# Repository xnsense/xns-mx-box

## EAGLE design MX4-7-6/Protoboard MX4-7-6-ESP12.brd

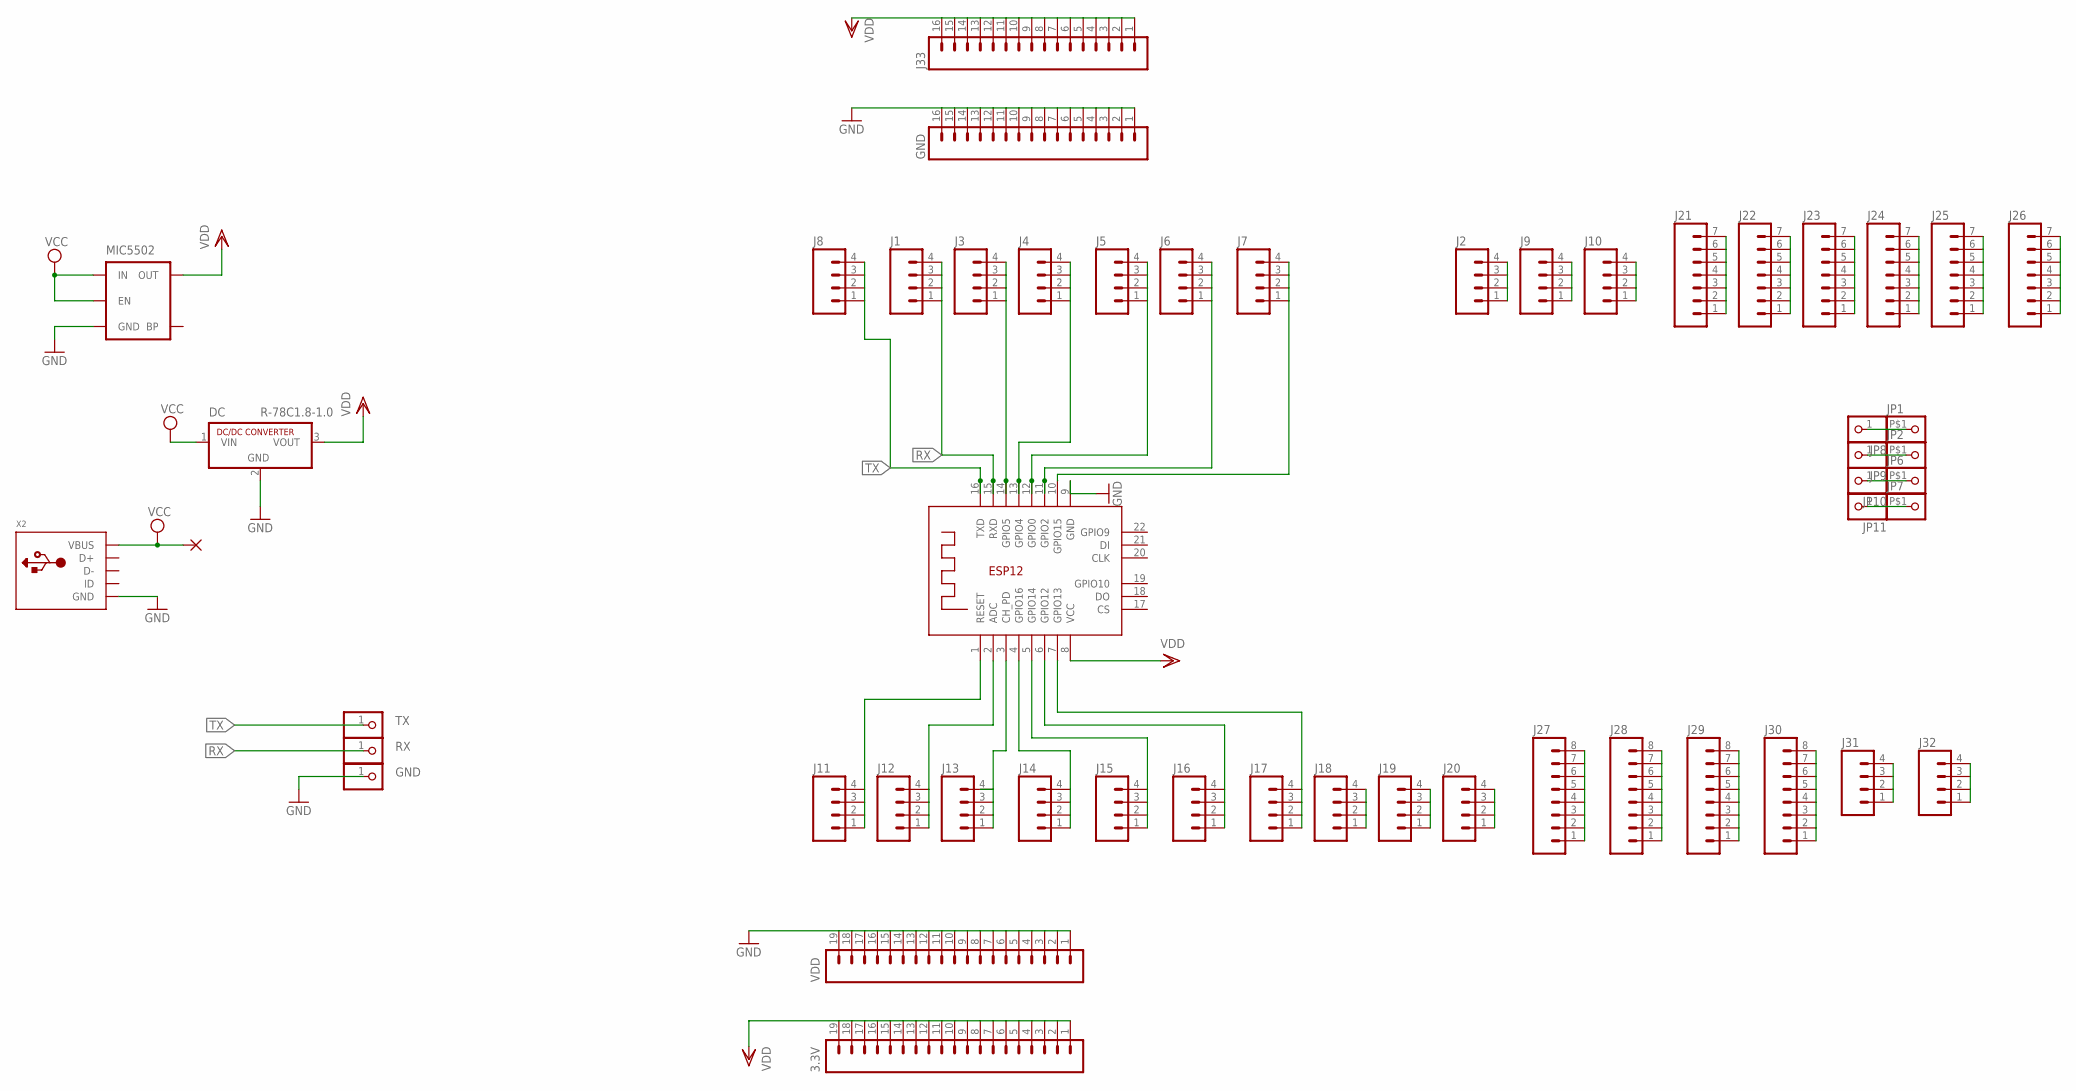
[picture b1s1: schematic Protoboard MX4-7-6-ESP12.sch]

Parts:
3.3V: M191X19_NO_SILK; 1X19_NO_SILK
5V: 1,6/0,8
DC: R-78C1.8-1.0; SIP3
GND: M161X16_NO_SILK; 1X16_NO_SILK
J1, J2, J3, J4, J5, J6, J7, J8, J9, J10, J11, J12, J13, J14, J15, J16, J17, J18, J19, J20, J31, J32: M04NO_SILK_ALL_ROUND; 1X04_NO_SILK_ALL_ROUND
J21, J22, J23, J24, J25, J26: M07NO_SILK; 1X07_NO_SILK
J27, J28, J29, J30: M08NO_SILK_FEMALE_PTH; 1X08_NO_SILK
J33: M161X16_NO_SILK; 1X16_NO_SILK
JP1, JP2, JP6, JP7: PINHD-1X1-BIGPOGO; 1X1-BIGPOGO
JP3: TX; 1X01-CLEANBIG
JP4: RX; 1X01-CLEANBIG
JP5: GND; 1X01-CLEANBIG
JP8, JP9, JP10, JP11: PINHD-1X1CB; 1X01-CLEANBIG
MIC5502: MIC52053.3V; SOT23-5
VDD: M191X19_NO_SILK; 1X19_NO_SILK
X1: ESP-12E
X2: USBMICRO_20329; 4UCONN_20329

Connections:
GND: DC.2 (GND), GND.1, GND.2, GND.3, GND.4, GND.5, GND.6, GND.7, GND.8, GND.9, GND.10, GND.11, GND.12, GND.13, GND.14, GND.15, GND.16, JP5.1, MIC5502.2 (GND), VDD.1, VDD.2, VDD.3, VDD.4, VDD.5, VDD.6, VDD.7, VDD.8, VDD.9, VDD.10, VDD.11, VDD.12, VDD.13, VDD.14, VDD.15, VDD.16, VDD.17, VDD.18, VDD.19, X1.9 (GND), X2.BASE@1 (GND), X2.BASE@2 (GND), X2.GND, X2.SPRT@1 (GND), X2.SPRT@2 (GND), X2.SPRT@3 (GND), X2.SPRT@4 (GND)
unnamed: J21.1, J21.2, J21.3, J21.4, J21.5, J21.6, J21.7
unnamed: J2.1, J2.2, J2.3, J2.4
unnamed: J3.1, J3.2, J3.3, J3.4, X1.14 (GPIO5)
unnamed: J4.1, J4.2, J4.3, J4.4, X1.13 (GPIO4)
unnamed: J5.1, J5.2, J5.3, J5.4, X1.12 (GPIO0)
unnamed: J6.1, J6.2, J6.3, J6.4, X1.11 (GPIO2)
unnamed: J7.1, J7.2, J7.3, J7.4, X1.10 (GPIO15)
unnamed: J9.1, J9.2, J9.3, J9.4
unnamed: J10.1, J10.2, J10.3, J10.4
unnamed: J18.1, J18.2, J18.3, J18.4
unnamed: J22.1, J22.2, J22.3, J22.4, J22.5, J22.6, J22.7
unnamed: J23.1, J23.2, J23.3, J23.4, J23.5, J23.6, J23.7
unnamed: J24.1, J24.2, J24.3, J24.4, J24.5, J24.6, J24.7
unnamed: J25.1, J25.2, J25.3, J25.4, J25.5, J25.6, J25.7
unnamed: J26.1, J26.2, J26.3, J26.4, J26.5, J26.6, J26.7
unnamed: J27.1, J27.2, J27.3, J27.4, J27.5, J27.6, J27.7, J27.8
unnamed: J19.1, J19.2, J19.3, J19.4
unnamed: J20.1, J20.2, J20.3, J20.4
unnamed: J28.1, J28.2, J28.3, J28.4, J28.5, J28.6, J28.7, J28.8
unnamed: J14.1, J14.2, J14.3, J14.4, X1.4 (GPIO16)
unnamed: J29.1, J29.2, J29.3, J29.4, J29.5, J29.6, J29.7, J29.8
unnamed: J30.1, J30.2, J30.3, J30.4, J30.5, J30.6, J30.7, J30.8
unnamed: J31.1, J31.2, J31.3, J31.4
unnamed: J32.1, J32.2, J32.3, J32.4
unnamed: JP1.P$1, JP8.1
unnamed: JP2.P$1, JP9.1
unnamed: JP6.P$1, JP10.1
unnamed: J17.1, J17.2, J17.3, J17.4, X1.7 (GPIO13)
unnamed: JP7.P$1, JP11.1
unnamed: J11.1, J11.2, J11.3, J11.4, X1.1 (RESET)
unnamed: J12.1, J12.2, J12.3, J12.4, X1.2 (ADC)
unnamed: J13.1, J13.2, J13.3, J13.4, X1.3 (CH_PD)
unnamed: J15.1, J15.2, J15.3, J15.4, X1.5 (GPIO14)
unnamed: J16.1, J16.2, J16.3, J16.4, X1.6 (GPIO12)
RX: J1.1, J1.2, J1.3, J1.4, JP4.1, X1.15 (RXD)
TX: J8.1, J8.2, J8.3, J8.4, JP3.1, X1.16 (TXD)
VCC: 5V.1, DC.1 (VIN), MIC5502.1 (IN), MIC5502.3 (EN), X2.VBUS
VDD: 3.3V.1, 3.3V.2, 3.3V.3, 3.3V.4, 3.3V.5, 3.3V.6, 3.3V.7, 3.3V.8, 3.3V.9, 3.3V.10, 3.3V.11, 3.3V.12, 3.3V.13, 3.3V.14, 3.3V.15, 3.3V.16, 3.3V.17, 3.3V.18, 3.3V.19, DC.3 (VOUT), J33.1, J33.2, J33.3, J33.4, J33.5, J33.6, J33.7, J33.8, J33.9, J33.10, J33.11, J33.12, J33.13, J33.14, J33.15, J33.16, MIC5502.5 (OUT), X1.8 (VCC)

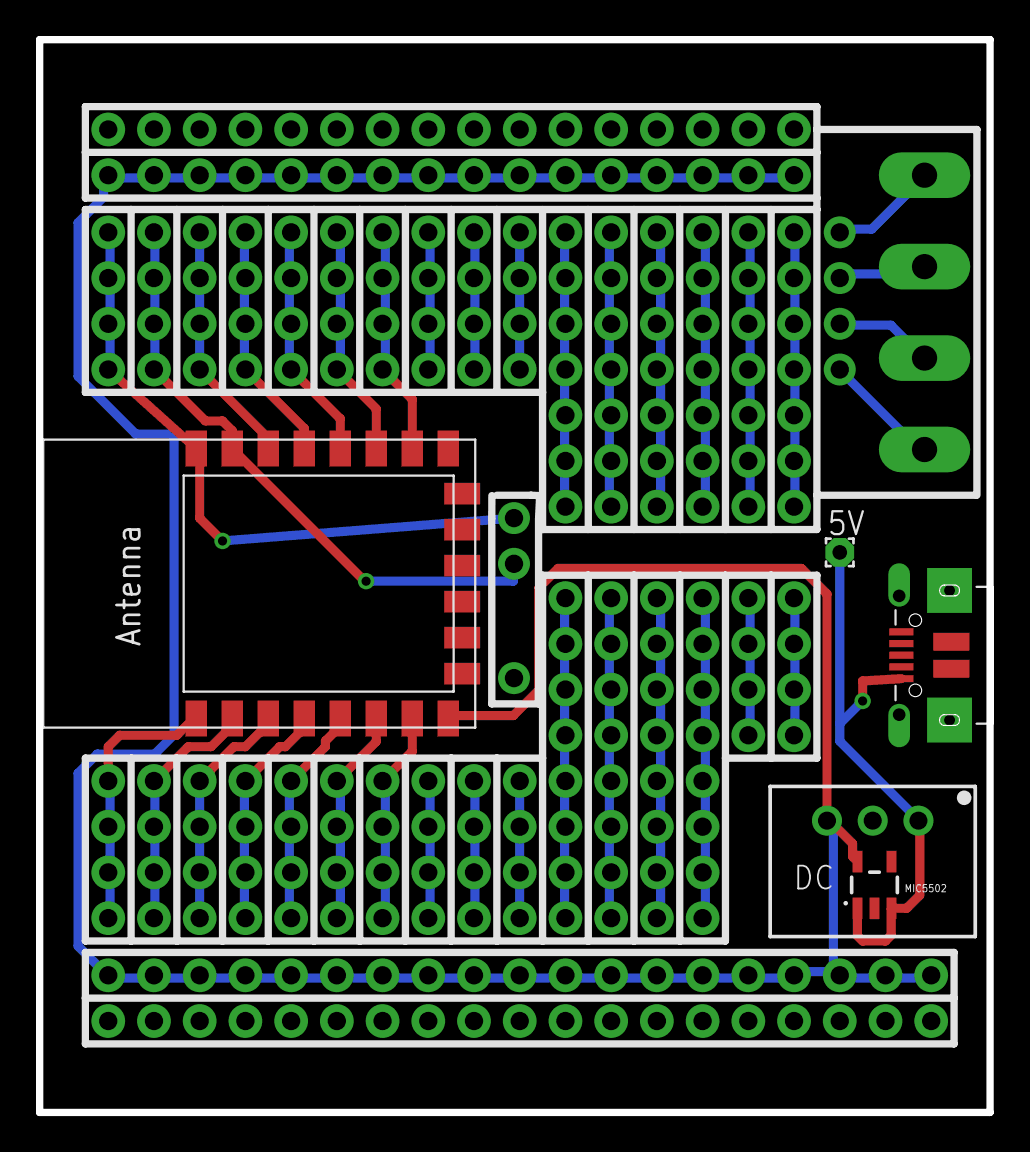
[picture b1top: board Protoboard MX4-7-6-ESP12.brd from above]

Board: 2 copper layers, 52.8 x 59.6 mm, 52 parts (0 on the bottom side), 39 nets.

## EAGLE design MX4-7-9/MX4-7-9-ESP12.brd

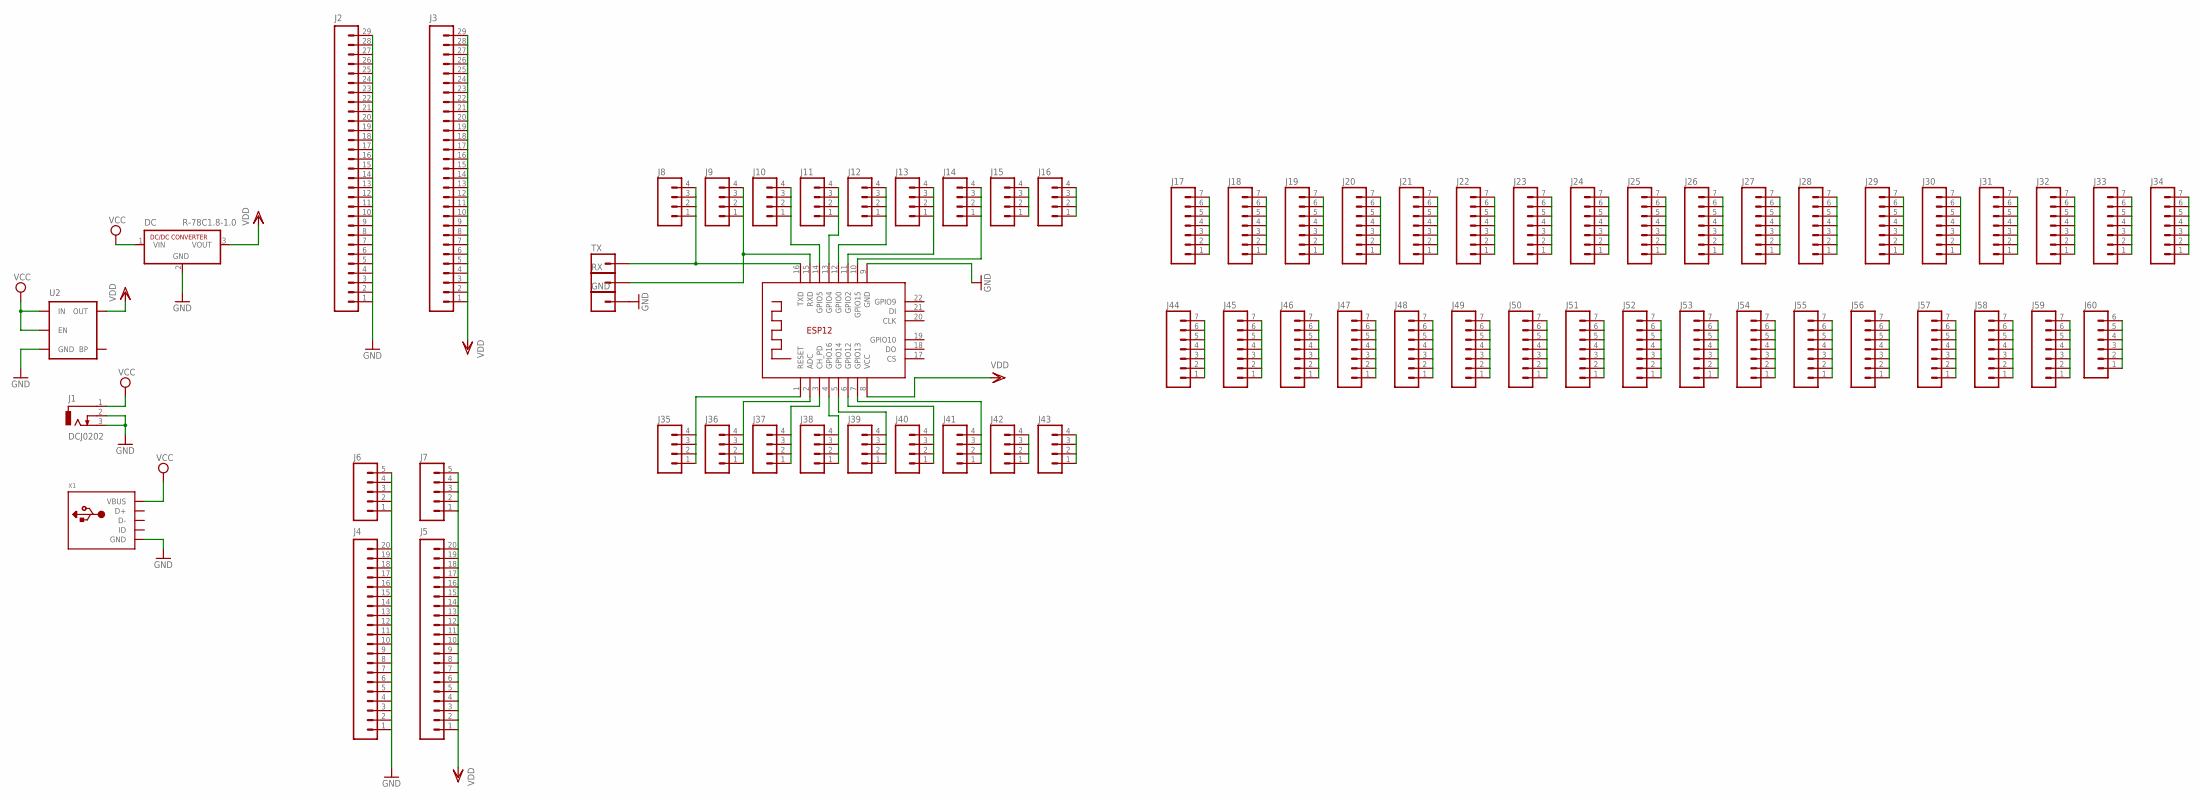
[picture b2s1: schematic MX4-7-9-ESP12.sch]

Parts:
DC: R-78C1.8-1.0; SIP3
GND: M01PTH_NO_SILK_YES_STOP; 1X01_NO_SILK
J1: DCJ0202
J2, J3: M29NO_SILK; 1X29_NO_SILK
J4, J5: M20NO_SILK_KIT; 1X20_NO_SILK_KIT
J6, J7: M05NO_SILK; 1X05_NO_SILK
J8, J9, J10, J11, J12, J13, J14, J15, J16, J35, J36, J37, J38, J39, J40, J41, J42, J43: M04NO_SILK_ALL_ROUND; 1X04_NO_SILK_ALL_ROUND
J17, J18, J19, J20, J21, J22, J23, J24, J25, J26, J27, J28, J29, J30, J31, J32, J33, J34, J44, J45, J46, J47, J48, J49, J50, J51, J52, J53, J54, J55, J56, J57, J58, J59: M07NO_SILK; 1X07_NO_SILK
J60: M06NO_SILK_FEMALE_PTH; 1X06_NO_SILK
RX: M01PTH_NO_SILK_YES_STOP; 1X01_NO_SILK
TX: M01PTH_NO_SILK_YES_STOP; 1X01_NO_SILK
U2: MIC52053.3V; SOT23-5
X1: USBMICRO_20329; 4UCONN_20329
X2: ESP-12E

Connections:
GND: DC.2 (GND), GND.1, J1.2, J1.3, J2.1, J2.2, J2.3, J2.4, J2.5, J2.6, J2.7, J2.8, J2.9, J2.10, J2.11, J2.12, J2.13, J2.14, J2.15, J2.16, J2.17, J2.18, J2.19, J2.20, J2.21, J2.22, J2.23, J2.24, J2.25, J2.26, J2.27, J2.28, J2.29, J4.1, J4.2, J4.3, J4.4, J4.5, J4.6, J4.7, J4.8, J4.9, J4.10, J4.11, J4.12, J4.13, J4.14, J4.15, J4.16, J4.17, J4.18, J4.19, J4.20, J6.1, J6.2, J6.3, J6.4, J6.5, U2.2 (GND), X1.BASE@1 (GND), X1.BASE@2 (GND), X1.GND, X1.SPRT@1 (GND), X1.SPRT@2 (GND), X1.SPRT@3 (GND), X1.SPRT@4 (GND), X2.9 (GND)
unnamed: J8.1, J8.2, J8.3, J8.4, TX.1, X2.16 (TXD)
unnamed: J9.1, J9.2, J9.3, J9.4, RX.1, X2.15 (RXD)
unnamed: J10.1, J10.2, J10.3, J10.4, X2.14 (GPIO5)
unnamed: J11.1, J11.2, J11.3, J11.4, X2.13 (GPIO4)
unnamed: J12.1, J12.2, J12.3, J12.4, X2.12 (GPIO0)
unnamed: J13.1, J13.2, J13.3, J13.4, X2.11 (GPIO2)
unnamed: J14.1, J14.2, J14.3, J14.4, X2.10 (GPIO15)
unnamed: J15.1, J15.2, J15.3, J15.4
unnamed: J16.1, J16.2, J16.3, J16.4
unnamed: J17.1, J17.2, J17.3, J17.4, J17.5, J17.6, J17.7
unnamed: J18.1, J18.2, J18.3, J18.4, J18.5, J18.6, J18.7
unnamed: J19.1, J19.2, J19.3, J19.4, J19.5, J19.6, J19.7
unnamed: J20.1, J20.2, J20.3, J20.4, J20.5, J20.6, J20.7
unnamed: J21.1, J21.2, J21.3, J21.4, J21.5, J21.6, J21.7
unnamed: J22.1, J22.2, J22.3, J22.4, J22.5, J22.6, J22.7
unnamed: J23.1, J23.2, J23.3, J23.4, J23.5, J23.6, J23.7
unnamed: J24.1, J24.2, J24.3, J24.4, J24.5, J24.6, J24.7
unnamed: J25.1, J25.2, J25.3, J25.4, J25.5, J25.6, J25.7
unnamed: J26.1, J26.2, J26.3, J26.4, J26.5, J26.6, J26.7
unnamed: J27.1, J27.2, J27.3, J27.4, J27.5, J27.6, J27.7
unnamed: J28.1, J28.2, J28.3, J28.4, J28.5, J28.6, J28.7
unnamed: J29.1, J29.2, J29.3, J29.4, J29.5, J29.6, J29.7
unnamed: J30.1, J30.2, J30.3, J30.4, J30.5, J30.6, J30.7
unnamed: J31.1, J31.2, J31.3, J31.4, J31.5, J31.6, J31.7
unnamed: J35.1, J35.2, J35.3, J35.4, X2.1 (RESET)
unnamed: J32.1, J32.2, J32.3, J32.4, J32.5, J32.6, J32.7
unnamed: J33.1, J33.2, J33.3, J33.4, J33.5, J33.6, J33.7
unnamed: J34.1, J34.2, J34.3, J34.4, J34.5, J34.6, J34.7
unnamed: J36.1, J36.2, J36.3, J36.4, X2.2 (ADC)
unnamed: J37.1, J37.2, J37.3, J37.4, X2.3 (CH_PD)
unnamed: J38.1, J38.2, J38.3, J38.4, X2.4 (GPIO16)
unnamed: J39.1, J39.2, J39.3, J39.4, X2.5 (GPIO14)
unnamed: J40.1, J40.2, J40.3, J40.4, X2.6 (GPIO12)
unnamed: J41.1, J41.2, J41.3, J41.4, X2.7 (GPIO13)
unnamed: J42.1, J42.2, J42.3, J42.4
unnamed: J43.1, J43.2, J43.3, J43.4
unnamed: J44.1, J44.2, J44.3, J44.4, J44.5, J44.6, J44.7
unnamed: J45.1, J45.2, J45.3, J45.4, J45.5, J45.6, J45.7
unnamed: J46.1, J46.2, J46.3, J46.4, J46.5, J46.6, J46.7
unnamed: J47.1, J47.2, J47.3, J47.4, J47.5, J47.6, J47.7
unnamed: J48.1, J48.2, J48.3, J48.4, J48.5, J48.6, J48.7
unnamed: J49.1, J49.2, J49.3, J49.4, J49.5, J49.6, J49.7
unnamed: J50.1, J50.2, J50.3, J50.4, J50.5, J50.6, J50.7
unnamed: J51.1, J51.2, J51.3, J51.4, J51.5, J51.6, J51.7
unnamed: J52.1, J52.2, J52.3, J52.4, J52.5, J52.6, J52.7
unnamed: J53.1, J53.2, J53.3, J53.4, J53.5, J53.6, J53.7
unnamed: J54.1, J54.2, J54.3, J54.4, J54.5, J54.6, J54.7
unnamed: J55.1, J55.2, J55.3, J55.4, J55.5, J55.6, J55.7
unnamed: J56.1, J56.2, J56.3, J56.4, J56.5, J56.6, J56.7
unnamed: J57.1, J57.2, J57.3, J57.4, J57.5, J57.6, J57.7
unnamed: J58.1, J58.2, J58.3, J58.4, J58.5, J58.6, J58.7
unnamed: J59.1, J59.2, J59.3, J59.4, J59.5, J59.6, J59.7
unnamed: J60.1, J60.2, J60.3, J60.4, J60.5, J60.6
VCC: DC.1 (VIN), J1.1, U2.1 (IN), U2.3 (EN), X1.VBUS
VDD: DC.3 (VOUT), J3.1, J3.2, J3.3, J3.4, J3.5, J3.6, J3.7, J3.8, J3.9, J3.10, J3.11, J3.12, J3.13, J3.14, J3.15, J3.16, J3.17, J3.18, J3.19, J3.20, J3.21, J3.22, J3.23, J3.24, J3.25, J3.26, J3.27, J3.28, J3.29, J5.1, J5.2, J5.3, J5.4, J5.5, J5.6, J5.7, J5.8, J5.9, J5.10, J5.11, J5.12, J5.13, J5.14, J5.15, J5.16, J5.17, J5.18, J5.19, J5.20, J7.1, J7.2, J7.3, J7.4, J7.5, U2.5 (OUT), X2.8 (VCC)

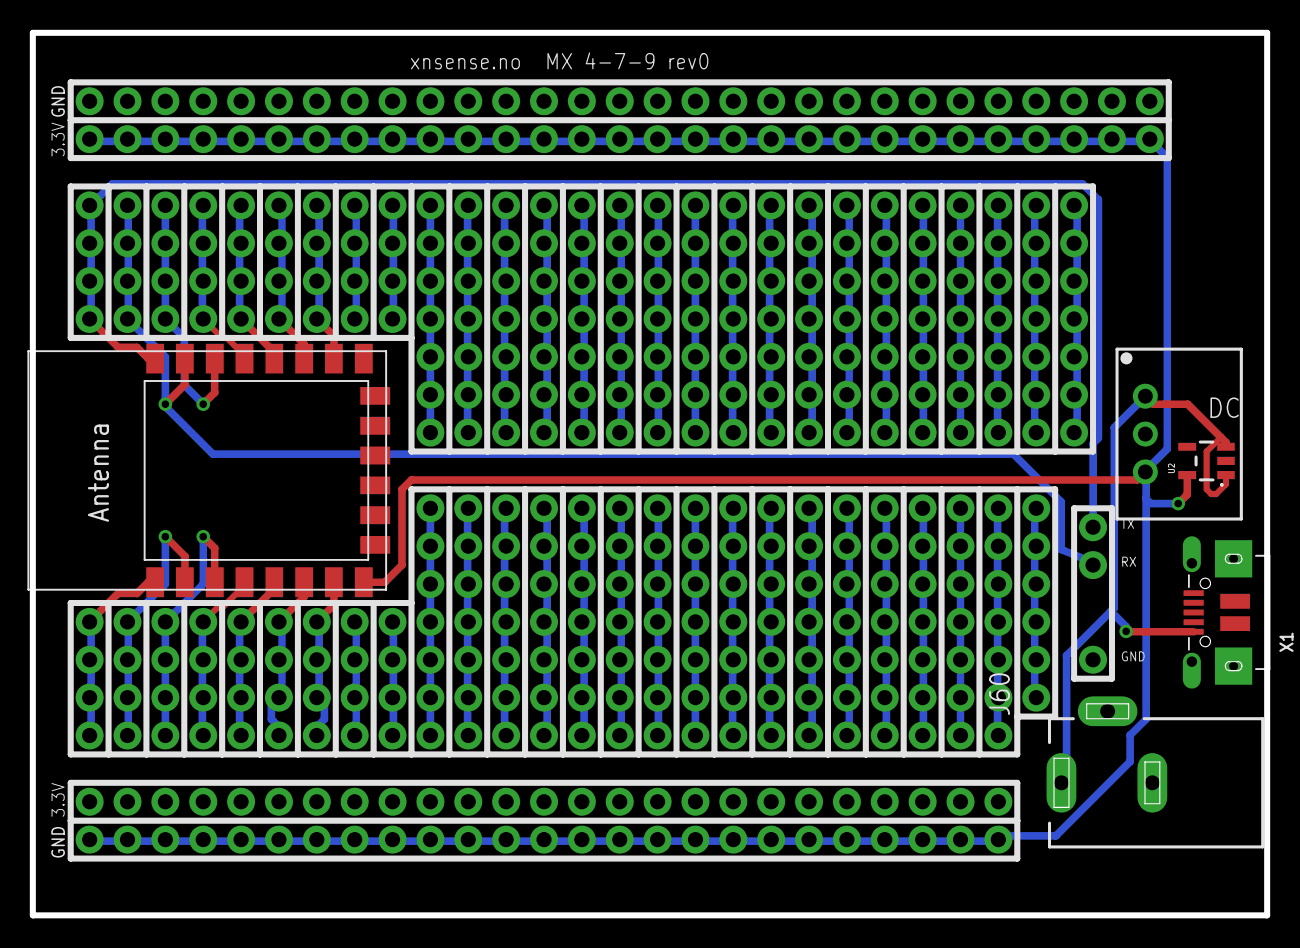
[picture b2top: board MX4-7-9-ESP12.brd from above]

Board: 2 copper layers, 82.8 x 59.2 mm, 67 parts (0 on the bottom side), 56 nets.

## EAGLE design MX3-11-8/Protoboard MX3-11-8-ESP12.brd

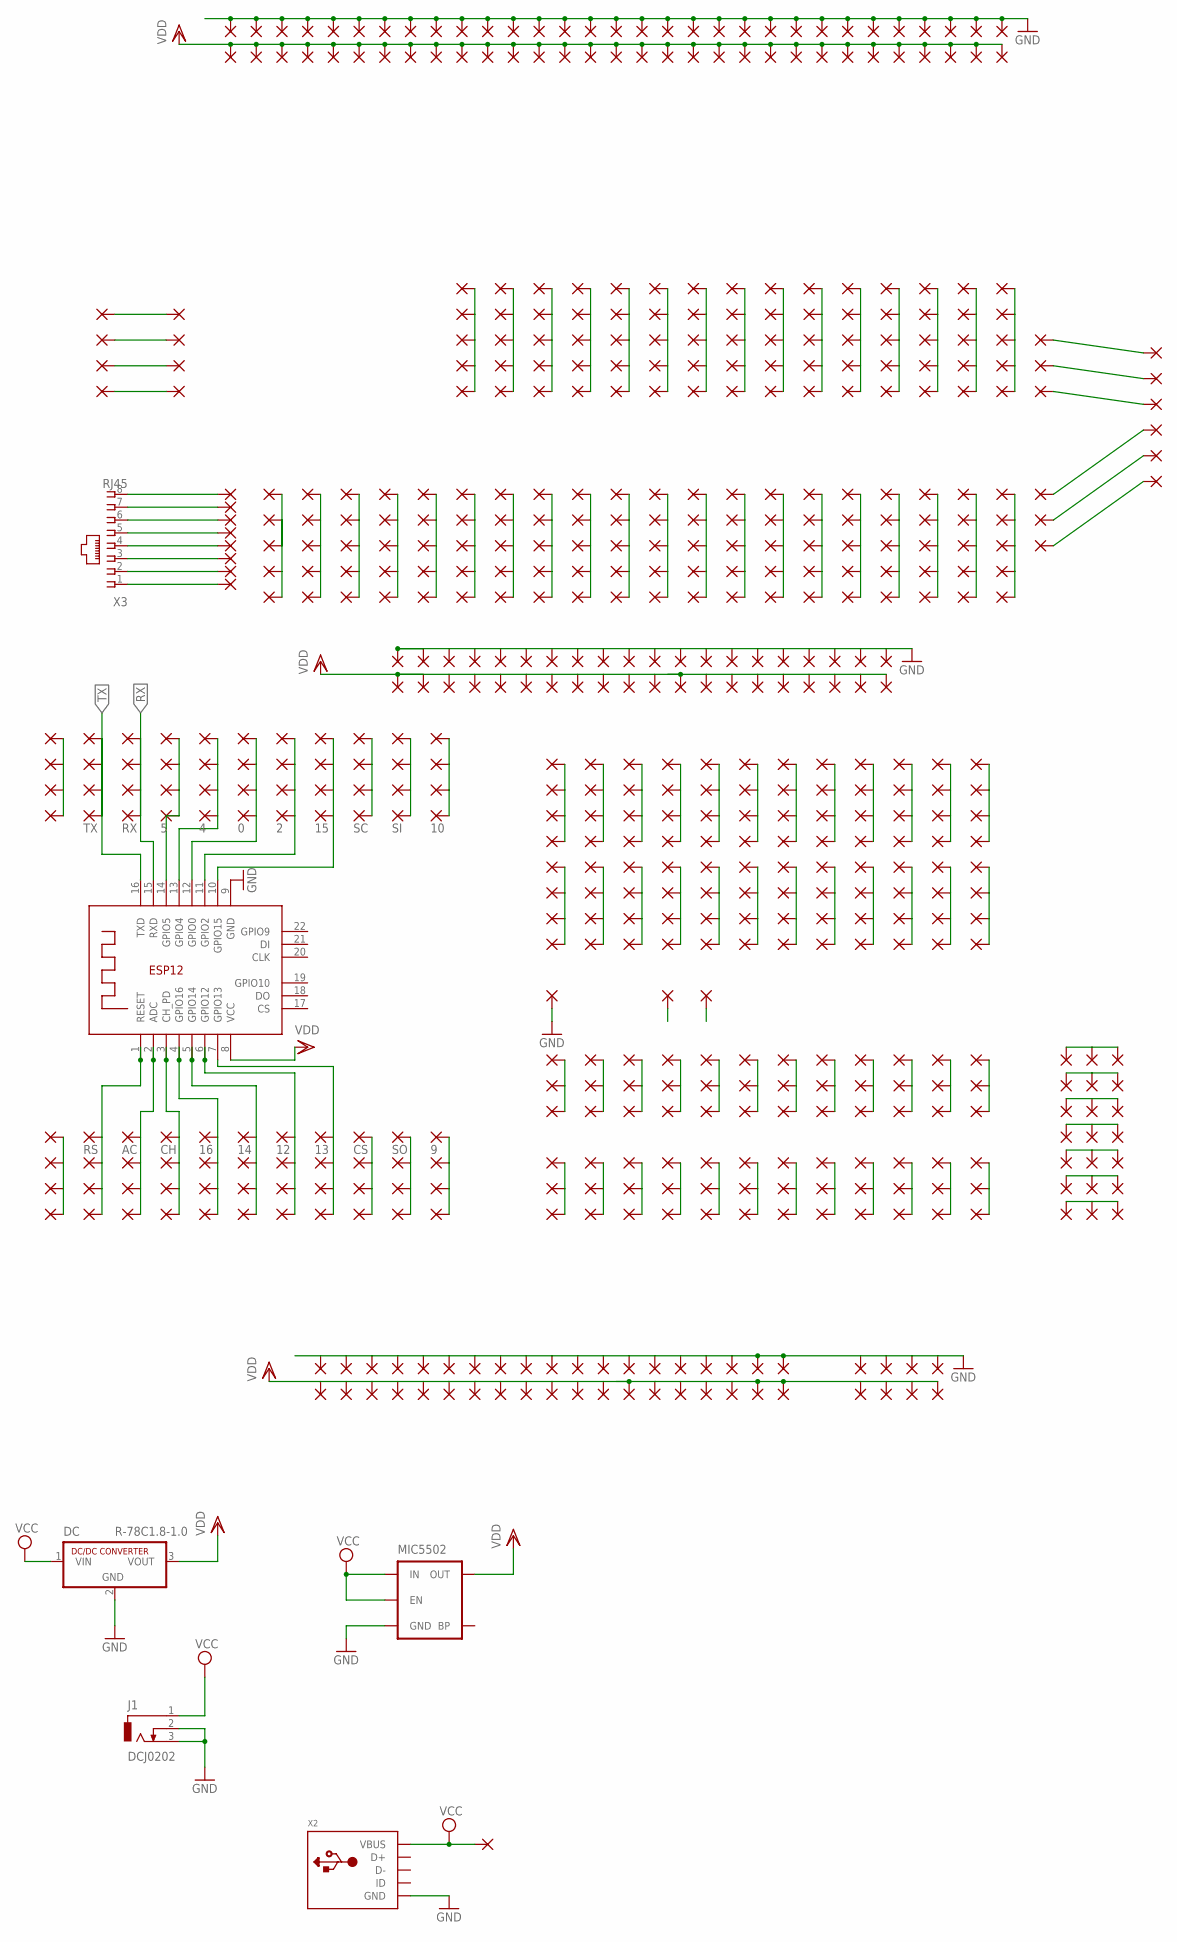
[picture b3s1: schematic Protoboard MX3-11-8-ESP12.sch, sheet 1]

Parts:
1, 2, 4, 5, 5V, 6, 7, 8: 1,6/0,8
DC: R-78C1.8-1.0; SIP3
J1: DCJ0202
MIC5502: MIC52053.3V; SOT23-5
PAD1, PAD2, PAD3, PAD4, PAD5, PAD6, PAD7, PAD8, PAD9, PAD10, PAD11, PAD12, PAD13, PAD14, PAD15, PAD16, PAD17, PAD18, PAD19, PAD20, PAD21, PAD22, PAD23, PAD24, PAD25, PAD26, PAD27, PAD28, PAD29, PAD30, PAD31, PAD32, PAD33, PAD34, PAD35, PAD36, PAD37, PAD38, PAD39, PAD40, PAD41, PAD42, PAD45, PAD46, PAD47, PAD48, PAD52, PAD53, PAD54, PAD55, PAD59, PAD60, PAD61, PAD62, PAD63, PAD64, PAD65, PAD66, PAD67, PAD68, PAD69, PAD70, PAD71, PAD72, PAD73, PAD74, PAD75, PAD76, PAD77, PAD78, PAD79, PAD80, PAD81, PAD82, PAD83, PAD84, PAD85, PAD86, PAD88, PAD89, PAD90, PAD91, PAD92, PAD93, PAD94, PAD97, PAD98, PAD99, PAD100, PAD101, PAD102, PAD103, PAD106, PAD107, PAD108, PAD109, PAD110, PAD111, PAD112, PAD115, PAD116, PAD117, PAD118, PAD119, PAD120, PAD121, PAD122, PAD123, PAD124, PAD125, PAD126, PAD128, PAD129, PAD130, PAD131, PAD132, PAD133, PAD134, PAD135, PAD137, PAD138, PAD139, PAD140, PAD141, PAD142, PAD143, PAD144, PAD146, PAD147, PAD148, PAD149, PAD150, PAD151, PAD152, PAD153, PAD155, PAD156, PAD157, PAD158, PAD159, PAD160, PAD161, PAD162, PAD164, PAD165, PAD166, PAD167, PAD168, PAD169, PAD170, PAD171, PAD173, PAD174, PAD175, PAD176, PAD177, PAD178, PAD179, PAD180, PAD182, PAD183, PAD184, PAD185, PAD186, PAD194, PAD195, PAD196, PAD197, PAD198, PAD199, PAD200, PAD201, PAD202, PAD203, PAD204, PAD205, PAD206, PAD207, PAD208, PAD209, PAD210, PAD211, PAD212, PAD213, PAD214, PAD215, PAD216, PAD217, PAD218, PAD219, PAD220, PAD221, PAD222, PAD223, PAD224, PAD225, PAD226, PAD227, PAD228, PAD229, PAD230, PAD231, PAD232, PAD233, PAD234, PAD235, PAD236, PAD237, PAD238, PAD239, PAD240, PAD249, PAD250, PAD251, PAD252, PAD253, PAD254, PAD255, PAD256, PAD257, PAD258, PAD267, PAD268, PAD276, PAD277, PAD285, PAD286, PAD294, PAD295, PAD303, PAD304, PAD312, PAD313, PAD321, PAD322, PAD323, PAD324, PAD325, PAD326, PAD327, PAD328, PAD329, PAD330, PAD331, PAD339, PAD340, PAD348, PAD349, PAD357, PAD358, PAD366, PAD367, PAD375, PAD376, PAD384, PAD390, PAD395, PAD396, PAD398, PAD399, PAD400, PAD402, PAD403, PAD404, PAD406, PAD407, PAD408, PAD410, PAD411, PAD412, PAD414, PAD415, PAD416, PAD417, PAD418, PAD419, PAD420, PAD421, PAD422, PAD423, PAD424, PAD425, PAD426, PAD427, PAD428, PAD429, PAD430, PAD431, PAD432, PAD433, PAD434, PAD435, PAD436, PAD437, PAD438, PAD439, PAD440, PAD441, PAD442, PAD443, PAD444, PAD445, PAD446, PAD447, PAD448, PAD449, PAD450, PAD451, PAD452, PAD453, PAD454, PAD455, PAD456, PAD457, PAD458, PAD459, PAD460, PAD461, PAD462, PAD463, PAD471, PAD472, PAD473, PAD474, PAD475, PAD476, PAD477, PAD478, PAD479, PAD480, PAD481, PAD482, PAD483, PAD484, PAD485, PAD486, PAD487, PAD488, PAD489, PAD490, PAD491, PAD492, PAD493, PAD494, PAD495, PAD496, PAD497, PAD498, PAD499, PAD500, PAD501, PAD502, PAD503, PAD504, PAD505, PAD506, PAD507, PAD508, PAD509, PAD510, PAD511, PAD512, PAD513, PAD514, PAD515, PAD516, PAD517, PAD518, PAD519, PAD520, PAD521, PAD522, PAD523, PAD524, PAD525, PAD526, PAD527, PAD528, PAD529, PAD530, PAD531, PAD532, PAD533, PAD534, PAD535, PAD536, PAD537, PAD538, PAD539, PAD540, PAD541, PAD542, PAD543, PAD544, PAD547, PAD548, PAD549, PAD550, PAD551, PAD554, PAD555, PAD556, PAD557, PAD558, PAD560, PAD561, PAD562, PAD563, PAD564, PAD565, PAD566, PAD567, PAD568, PAD569, PAD570, PAD571, PAD572, PAD573, PAD574, PAD575, PAD576, PAD577, PAD578, PAD579, PAD580, PAD581, PAD582, PAD583, PAD584, PAD585, PAD586, PAD587, PAD588, PAD589, PAD590, PAD591, PAD592, PAD593, PAD594, PAD595, PAD596, PAD597, PAD598, PAD599, PAD600, PAD601, PAD602, PAD603, PAD604, PAD605, PAD606, PAD607, PAD608, PAD609, PAD610, PAD611, PAD612, PAD613, PAD614, PAD615, PAD617, PAD618, PAD619, PAD620, PAD621, PAD623, PAD624, PAD625, PAD628, PAD629, PAD630, PAD632, PAD633, PAD634, PAD636, PAD637, PAD638, PAD640, PAD641, PAD642, PAD643, PAD644, PAD645, PAD646, PAD647, PAD648, PAD649, PAD650, PAD651, PAD652, PAD653, PAD654, PAD655, PAD656, PAD657, PAD658, PAD659, PAD660, PAD661, PAD662, PAD663, PAD664, PAD665, PAD666, PAD667, PAD668, PAD669, PAD670, PAD671, PAD672, PAD673, PAD674, PAD675, PAD676, PAD679, PAD680, PAD681, PAD682, PAD683, PAD686, PAD687, PAD688, PAD689, PAD690, PAD693, PAD694, PAD695, PAD696, PAD697, PAD700, PAD701, PAD702, PAD703, PAD704, PAD707, PAD708, PAD709, PAD710, PAD711, PAD714, PAD715, PAD716, PAD717, PAD718, PAD721, PAD722, PAD723, PAD724, PAD725, PAD728, PAD729, PAD730, PAD731, PAD732, PAD734, PAD743, PAD744, PAD745, PAD747, PAD748, PAD749, PAD757, PAD759, PAD760, PAD761, PAD762, PAD763, PAD764, PAD766, PAD767, PAD768, PAD771, PAD772, PAD773, PAD775, PAD776, PAD777, PAD779, PAD780, PAD781, PAD783, PAD784, PAD785, PAD786, PAD787, PAD788, PAD789, PAD790, PAD792, PAD793, PAD794: 1,6/0,8
PAD241, PAD242, PAD243, PAD244, PAD751, PAD752, PAD753, PAD754, PAD755, PAD756: 3,17/1,3
PAD259: TX; 1,6/0,8
PAD397: RX; 1,6/0,8
PAD401: 5; 1,6/0,8
PAD405: 4; 1,6/0,8
PAD409: 0; 1,6/0,8
PAD413: 2; 1,6/0,8
PAD622: 15; 1,6/0,8
PAD626: SC; 1,6/0,8
PAD627: AC; 1,6/0,8
PAD631: CH; 1,6/0,8
PAD635: 16; 1,6/0,8
PAD639: 14; 1,6/0,8
PAD742: 12; 1,6/0,8
PAD746: 13; 1,6/0,8
PAD758: CS; 1,6/0,8
PAD765: SI; 1,6/0,8
PAD769: 10; 1,6/0,8
PAD770: RS; 1,6/0,8
PAD774: SO; 1,6/0,8
PAD778: 9; 1,6/0,8
RJ-3: 1,6/0,8
RX: 1,6/0,8
TX: 1,6/0,8
X1: ESP-12E
X2: USBMICRO_20329; 4UCONN_20329
X3: RJ45; RJ45-NO-SHIELD

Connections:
GND: DC.2 (GND), J1.2, J1.3, MIC5502.2 (GND), PAD4.1, PAD12.1, PAD17.1, PAD22.1, PAD23.1, PAD24.1, PAD25.1, PAD26.1, PAD27.1, PAD28.1, PAD29.1, PAD30.1, PAD31.1, PAD32.1, PAD33.1, PAD36.1, PAD38.1, PAD54.1, PAD118.1, PAD140.1, PAD141.1, PAD149.1, PAD249.1, PAD255.1, PAD276.1, PAD277.1, PAD285.1, PAD286.1, PAD326.1, PAD327.1, PAD328.1, PAD329.1, PAD330.1, PAD331.1, PAD339.1, PAD421.1, PAD422.1, PAD423.1, PAD424.1, PAD425.1, PAD426.1, PAD427.1, PAD428.1, PAD429.1, PAD430.1, PAD431.1, PAD432.1, PAD433.1, PAD434.1, PAD435.1, PAD436.1, PAD439.1, PAD440.1, PAD441.1, PAD447.1, PAD471.1, PAD472.1, PAD473.1, PAD474.1, PAD475.1, PAD476.1, PAD477.1, PAD478.1, PAD479.1, PAD525.1, PAD619.1, PAD620.1, PAD621.1, PAD643.1, PAD734.1, PAD757.1, PAD783.1, PAD788.1, PAD789.1, PAD790.1, X1.9 (GND), X2.BASE@1 (GND), X2.BASE@2 (GND), X2.GND, X2.SPRT@1 (GND), X2.SPRT@2 (GND), X2.SPRT@3 (GND), X2.SPRT@4 (GND)
unnamed: PAD97.1, PAD98.1, PAD99.1
unnamed: PAD34.1, PAD35.1, PAD37.1, PAD40.1
unnamed: PAD45.1, PAD46.1, PAD47.1
unnamed: PAD106.1, PAD107.1, PAD108.1
unnamed: PAD59.1, PAD60.1, PAD61.1
unnamed: PAD83.1, PAD84.1, PAD85.1
unnamed: PAD92.1, PAD93.1, PAD94.1
unnamed: PAD101.1, PAD102.1, PAD103.1
unnamed: PAD110.1, PAD111.1, PAD112.1
unnamed: PAD115.1, PAD116.1, PAD117.1
unnamed: PAD124.1, PAD125.1, PAD126.1
unnamed: PAD133.1, PAD134.1, PAD135.1
unnamed: PAD142.1, PAD143.1, PAD144.1
unnamed: PAD151.1, PAD152.1, PAD153.1
unnamed: PAD160.1, PAD161.1, PAD162.1
unnamed: PAD169.1, PAD170.1, PAD171.1
unnamed: PAD178.1, PAD179.1, PAD180.1
unnamed: PAD42.1, PAD241.1
unnamed: PAD199.1, PAD200.1, PAD201.1, PAD202.1
unnamed: PAD208.1, PAD209.1, PAD210.1, PAD211.1
unnamed: PAD217.1, PAD218.1, PAD219.1, PAD220.1
unnamed: PAD66.1, PAD67.1, PAD68.1
unnamed: PAD73.1, PAD74.1, PAD75.1
unnamed: PAD41.1, PAD242.1
unnamed: PAD122.1, PAD123.1, PAD131.1, PAD132.1
unnamed: PAD39.1, PAD243.1
unnamed: PAD15.1, PAD244.1
unnamed: PAD762.1, PAD763.1, PAD764.1, PAD765.1
unnamed: PAD766.1, PAD767.1, PAD768.1, PAD769.1
unnamed: PAD167.1, PAD168.1, PAD176.1, PAD177.1
unnamed: PAD79.1, PAD80.1, PAD81.1
unnamed: PAD88.1, PAD89.1, PAD90.1
unnamed: PAD119.1, PAD120.1, PAD121.1
unnamed: PAD195.1, PAD203.1, PAD204.1, PAD212.1
unnamed: PAD250.1, PAD251.1, PAD252.1, PAD253.1, PAD254.1
unnamed: PAD398.1, PAD399.1, PAD400.1, PAD401.1, X1.14 (GPIO5)
unnamed: PAD402.1, PAD403.1, PAD404.1, PAD405.1, X1.13 (GPIO4)
unnamed: PAD223.1, PAD224.1, PAD225.1, PAD226.1
unnamed: PAD230.1, PAD231.1, PAD232.1, PAD233.1
unnamed: PAD237.1, PAD238.1, PAD239.1, PAD240.1
unnamed: PAD406.1, PAD407.1, PAD408.1, PAD409.1, X1.12 (GPIO0)
unnamed: PAD410.1, PAD411.1, PAD412.1, PAD413.1, X1.11 (GPIO2)
unnamed: PAD417.1, PAD418.1, PAD419.1, PAD622.1, X1.10 (GPIO15)
unnamed: PAD623.1, PAD624.1, PAD625.1, PAD626.1
unnamed: PAD639.1, PAD640.1, PAD641.1, PAD642.1, X1.5 (GPIO14)
unnamed: PAD758.1, PAD759.1, PAD760.1, PAD761.1
unnamed: PAD357.1, PAD358.1, PAD366.1, PAD367.1
unnamed: PAD390.1, PAD395.1, PAD414.1, PAD415.1
unnamed: PAD438.1, PAD457.1, PAD458.1, PAD463.1
unnamed: 2.1, X3.1
unnamed: RJ-3.1, X3.2
unnamed: 4.1, X3.3
unnamed: PAD491.1, PAD492.1, PAD493.1, PAD494.1, PAD495.1
unnamed: PAD498.1, PAD499.1, PAD500.1, PAD501.1, PAD502.1
unnamed: PAD505.1, PAD506.1, PAD507.1, PAD508.1, PAD509.1
unnamed: PAD512.1, PAD513.1, PAD514.1, PAD515.1, PAD516.1
unnamed: PAD519.1, PAD520.1, PAD521.1, PAD522.1, PAD523.1
unnamed: PAD526.1, PAD527.1, PAD528.1, PAD529.1, PAD530.1
unnamed: PAD533.1, PAD534.1, PAD535.1, PAD536.1, PAD537.1
unnamed: PAD540.1, PAD541.1, PAD542.1, PAD543.1, PAD544.1
unnamed: PAD547.1, PAD548.1, PAD549.1, PAD550.1, PAD551.1
unnamed: PAD554.1, PAD555.1, PAD556.1, PAD557.1, PAD558.1
unnamed: PAD561.1, PAD562.1, PAD563.1, PAD564.1, PAD565.1
unnamed: PAD568.1, PAD569.1, PAD570.1, PAD571.1, PAD572.1
unnamed: PAD575.1, PAD576.1, PAD577.1, PAD578.1, PAD579.1
unnamed: PAD582.1, PAD583.1, PAD584.1, PAD585.1, PAD586.1
unnamed: PAD589.1, PAD590.1, PAD591.1, PAD592.1, PAD593.1
unnamed: PAD596.1, PAD597.1, PAD598.1, PAD599.1, PAD600.1
unnamed: PAD603.1, PAD604.1, PAD605.1, PAD606.1, PAD607.1
unnamed: PAD610.1, PAD611.1, PAD612.1, PAD613.1, PAD614.1
unnamed: 5.1, X3.4
unnamed: PAD778.1, PAD779.1, PAD780.1, PAD781.1
unnamed: PAD770.1, PAD771.1, PAD772.1, PAD773.1, X1.1 (RESET)
unnamed: PAD627.1, PAD628.1, PAD629.1, PAD630.1, X1.2 (ADC)
unnamed: 6.1, X3.5
unnamed: PAD635.1, PAD636.1, PAD637.1, PAD638.1, X1.4 (GPIO16)
unnamed: PAD742.1, PAD743.1, PAD744.1, PAD745.1, X1.6 (GPIO12)
unnamed: PAD644.1, PAD645.1, PAD646.1, PAD647.1, PAD648.1
unnamed: PAD651.1, PAD652.1, PAD653.1, PAD654.1, PAD655.1
unnamed: PAD658.1, PAD659.1, PAD660.1, PAD661.1, PAD662.1
unnamed: PAD665.1, PAD666.1, PAD667.1, PAD668.1, PAD669.1
unnamed: PAD672.1, PAD673.1, PAD674.1, PAD675.1, PAD676.1
unnamed: PAD679.1, PAD680.1, PAD681.1, PAD682.1, PAD683.1
unnamed: PAD686.1, PAD687.1, PAD688.1, PAD689.1, PAD690.1
unnamed: PAD693.1, PAD694.1, PAD695.1, PAD696.1, PAD697.1
unnamed: PAD700.1, PAD701.1, PAD702.1, PAD703.1, PAD704.1
unnamed: PAD707.1, PAD708.1, PAD709.1, PAD710.1, PAD711.1
unnamed: 7.1, X3.6
unnamed: 8.1, X3.7
unnamed: 1.1, X3.8
unnamed: PAD518.1, PAD524.1, PAD531.1, PAD532.1, PAD538.1
unnamed: PAD560.1, PAD566.1, PAD567.1, PAD573.1
unnamed: PAD656.1, PAD756.1
unnamed: PAD657.1, PAD755.1
unnamed: PAD714.1, PAD715.1, PAD716.1, PAD717.1, PAD718.1
unnamed: PAD721.1, PAD722.1, PAD723.1, PAD724.1, PAD725.1
unnamed: PAD728.1, PAD729.1, PAD730.1, PAD731.1, PAD732.1
unnamed: PAD631.1, PAD632.1, PAD633.1, PAD634.1, X1.3 (CH_PD)
unnamed: PAD663.1, PAD754.1
unnamed: PAD664.1, PAD753.1
unnamed: PAD670.1, PAD752.1
unnamed: PAD671.1, PAD751.1
unnamed: PAD63.1, PAD64.1, PAD65.1
unnamed: PAD77.1, PAD78.1, PAD86.1
unnamed: PAD70.1, PAD71.1, PAD72.1
unnamed: PAD746.1, PAD747.1, PAD748.1, PAD749.1, X1.7 (GPIO13)
unnamed: PAD774.1, PAD775.1, PAD776.1, PAD777.1
unnamed: PAD164.1, PAD165.1, PAD166.1
unnamed: PAD182.1, PAD183.1, PAD184.1
unnamed: PAD173.1, PAD174.1, PAD175.1
unnamed: PAD128.1, PAD129.1, PAD130.1
unnamed: PAD137.1, PAD138.1, PAD139.1
unnamed: PAD146.1, PAD147.1, PAD148.1
unnamed: PAD155.1, PAD156.1, PAD157.1
unnamed: PAD214.1, PAD215.1, PAD216.1, PAD581.1
unnamed: PAD205.1, PAD206.1, PAD207.1, PAD580.1
unnamed: PAD1.1, PAD2.1, PAD3.1, PAD587.1
unnamed: PAD150.1, PAD158.1, PAD159.1, PAD588.1
unnamed: PAD185.1, PAD186.1, PAD194.1, PAD594.1
unnamed: PAD213.1, PAD221.1, PAD222.1, PAD595.1
unnamed: PAD227.1, PAD228.1, PAD229.1, PAD601.1
unnamed: PAD234.1, PAD235.1, PAD236.1, PAD602.1
unnamed: PAD340.1, PAD348.1, PAD349.1, PAD608.1
unnamed: PAD375.1, PAD376.1, PAD384.1, PAD609.1
unnamed: PAD416.1, PAD420.1, PAD437.1, PAD615.1
unnamed: PAD196.1, PAD197.1, PAD198.1, PAD574.1
unnamed: PAD48.1, PAD52.1, PAD53.1, PAD55.1, PAD62.1
unnamed: PAD69.1, PAD76.1, PAD82.1, PAD91.1, PAD100.1
RX: PAD267.1, PAD268.1, PAD396.1, PAD397.1, RX.1, X1.15 (RXD)
TX: PAD256.1, PAD257.1, PAD258.1, PAD259.1, TX.1, X1.16 (TXD)
VCC: 5V.1, DC.1 (VIN), J1.1, MIC5502.1 (IN), MIC5502.3 (EN), X2.VBUS
VDD: DC.3 (VOUT), MIC5502.5 (OUT), PAD5.1, PAD6.1, PAD7.1, PAD8.1, PAD9.1, PAD10.1, PAD11.1, PAD13.1, PAD14.1, PAD16.1, PAD18.1, PAD19.1, PAD20.1, PAD21.1, PAD109.1, PAD294.1, PAD295.1, PAD303.1, PAD304.1, PAD312.1, PAD313.1, PAD321.1, PAD322.1, PAD323.1, PAD324.1, PAD325.1, PAD442.1, PAD443.1, PAD444.1, PAD445.1, PAD446.1, PAD448.1, PAD449.1, PAD450.1, PAD451.1, PAD452.1, PAD453.1, PAD454.1, PAD455.1, PAD456.1, PAD459.1, PAD460.1, PAD461.1, PAD462.1, PAD480.1, PAD481.1, PAD482.1, PAD483.1, PAD484.1, PAD485.1, PAD486.1, PAD487.1, PAD488.1, PAD489.1, PAD490.1, PAD496.1, PAD497.1, PAD503.1, PAD504.1, PAD510.1, PAD511.1, PAD517.1, PAD539.1, PAD617.1, PAD618.1, PAD649.1, PAD650.1, PAD784.1, PAD785.1, PAD786.1, PAD787.1, PAD792.1, PAD793.1, PAD794.1, X1.8 (VCC)

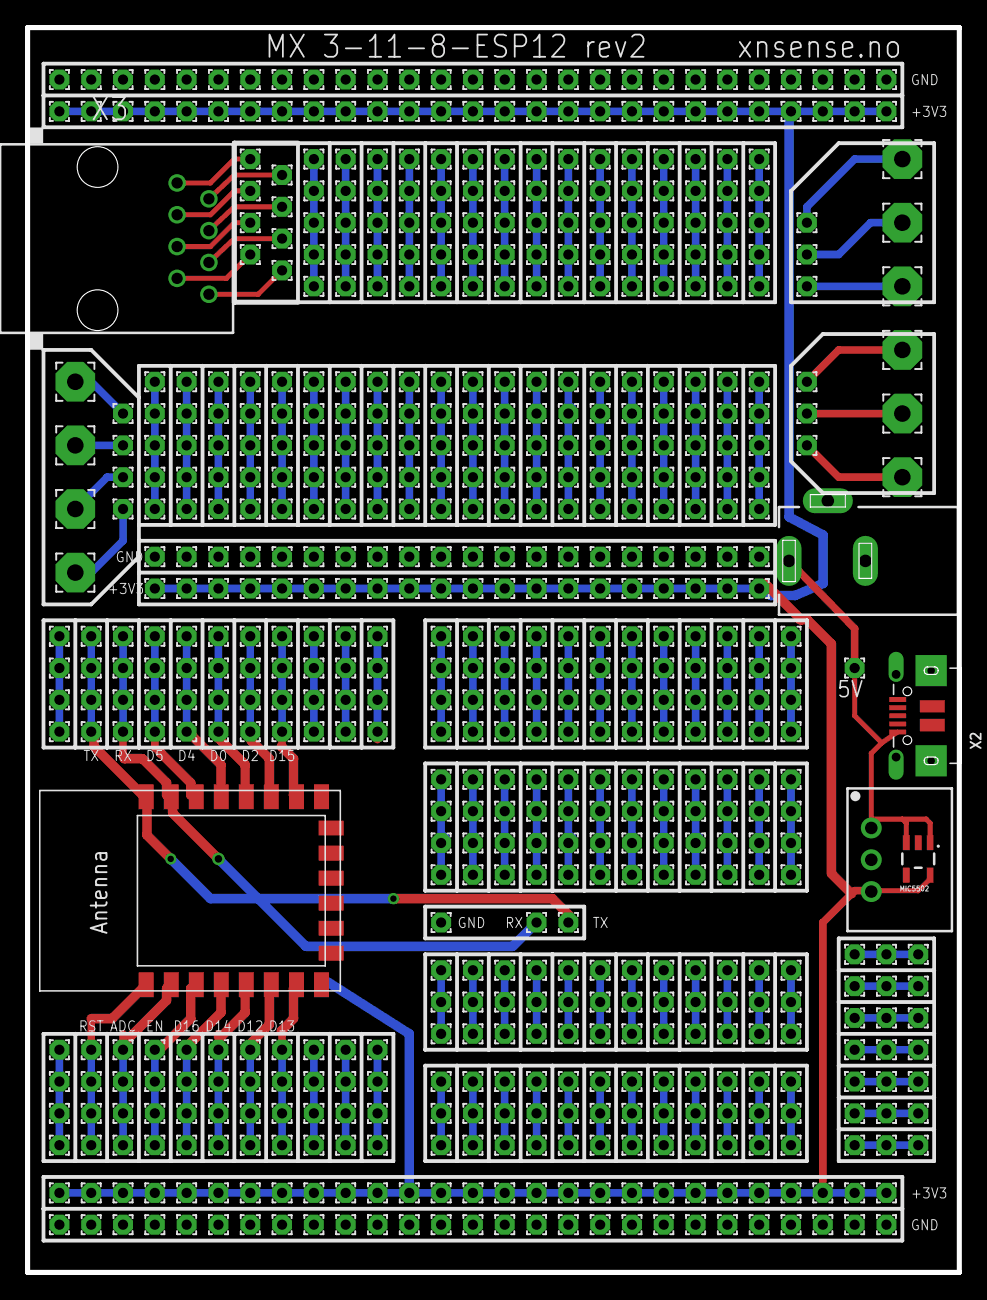
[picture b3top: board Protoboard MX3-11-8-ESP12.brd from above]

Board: 2 copper layers, 74.4 x 99.4 mm, 638 parts (0 on the bottom side), 133 nets.

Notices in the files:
parts and their libraries:
SparkFun-PowerIC: Licensing: Creative Commons ShareAlike 4.0 International - https://creativecommons.org/licenses/by-sa/4.0
